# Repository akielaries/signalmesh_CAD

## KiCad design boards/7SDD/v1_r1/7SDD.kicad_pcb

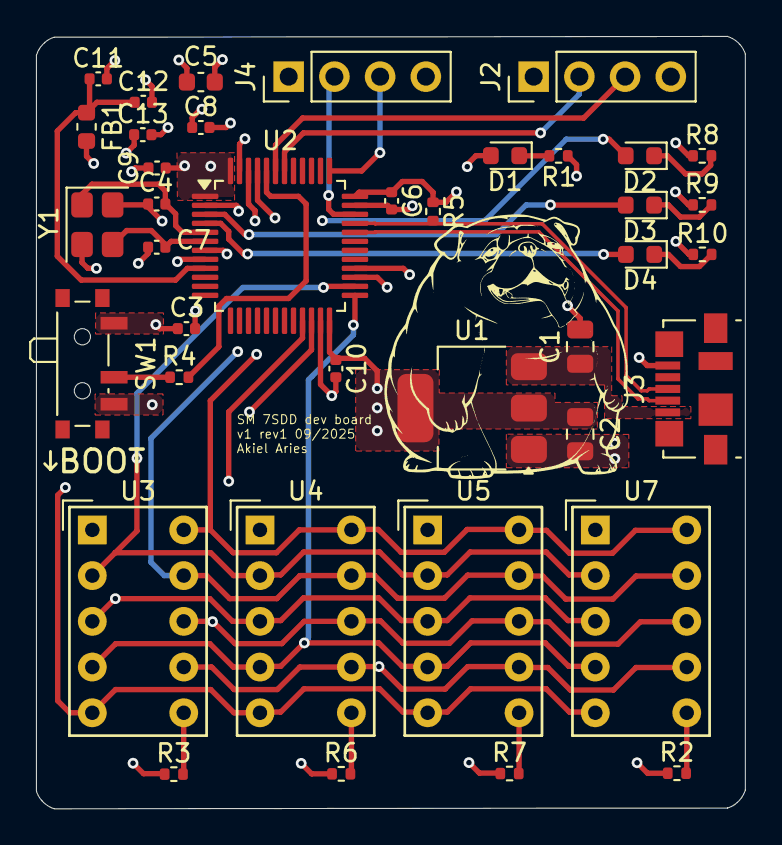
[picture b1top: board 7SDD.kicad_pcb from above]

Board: 4 copper layers, 39.4 x 42.9 mm, 39 parts (0 on the bottom side), 34 nets.

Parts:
C1, C2: 22u; C_0805_2012Metric
C3, C6, C8, C9, C10: 100n; C_0402_1005Metric
C4, C7: 10p; C_0402_1005Metric
C5: 10u; C_0603_1608Metric
C11: 10n; C_0402_1005Metric
C12, C13: 1u; C_0402_1005Metric
D1, D2: RED; LED_0603_1608Metric
D3: GREEN; LED_0603_1608Metric
D4: YEL; LED_0603_1608Metric
FB1: 120R; L_0603_1608Metric
J2: Conn_01x04_Pin; PinHeader_1x04_P2.54mm_Vertical
J3: USB_B_Micro; USB_Micro-B_Molex_47346-0001
J4: STLINK; PinHeader_1x04_P2.54mm_Vertical
R1, R8, R9, R10: 1k5; R_0402_1005Metric
R2, R3, R6, R7: 440; R_0402_1005Metric
R4: 10k; R_0402_1005Metric
R5: 1K5; R_0402_1005Metric
SW1: SW_SPDT; SW_SPDT_PCM12
U1: AMS1117-3.3; SOT-223-3_TabPin2
U2: STM32F103C8T6; LQFP-48_7x7mm_P0.5mm
U3, U4, U5, U7: HDSP-7501; HDSP-A151
Y1: 16 MHz; Crystal_SMD_3225-4Pin_3.2x2.5mm

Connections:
+3.3V: C2.1, C5.1, C6.1, C8.1, C9.1, C10.1, C13.1, D1.2 (A), FB1.2, J2.1, J4.1, R2.1, R3.1, R5.1, R6.1, R7.1, SW1.3 (C), U1.2 (VO), U2.1 (VBAT), U2.24 (VDD), U2.36 (VDD), U2.48 (VDD)
+3.3VA: C11.1, C12.1, FB1.1, U2.9 (VDDA)
/SEG_A: U2.45 (PB8), U3.10 (A), U4.10 (A), U5.10 (A), U7.10 (A)
/SEG_B: U2.46 (PB9), U3.9 (B), U4.9 (B), U5.9 (B), U7.9 (B)
/SEG_C: U2.21 (PB10), U3.8 (C), U4.8 (C), U5.8 (C), U7.8 (C)
/SEG_D: U2.22 (PB11), U3.5 (D), U4.5 (D), U5.5 (D), U7.5 (D)
/SEG_DP: U2.28 (PB15), U3.7 (DP), U4.7 (DP), U5.7 (DP), U7.7 (DP)
/SEG_E: U2.25 (PB12), U3.4 (E), U4.4 (E), U5.4 (E), U7.4 (E)
/SEG_F: U2.26 (PB13), U3.2 (F), U4.2 (F), U5.2 (F), U7.2 (F)
/SEG_G: U2.27 (PB14), U3.3 (G), U4.3 (G), U5.3 (G), U7.3 (G)
/STM32F103/BOOT0: R4.2, U2.44 (BOOT0)
/STM32F103/HSE_IN: C4.1, U2.5 (PD0), Y1.1
/STM32F103/HSE_OUT: C7.1, U2.6 (PD1), Y1.3
/STM32F103/LED1: D2.2 (A), U2.2 (PC13)
/STM32F103/LED2: D3.2 (A), U2.3 (PC14)
/STM32F103/LED3: D4.2 (A), U2.4 (PC15)
/STM32F103/NRST: C3.1, U2.7 (NRST)
/STM32F103/POWER_LED: D1.1 (K), R1.2
/STM32F103/SWCLK: J4.3, U2.37 (PA14)
/STM32F103/SWDIO: J4.2, U2.34 (PA13)
/STM32F103/SW_BOOT0: R4.1, SW1.2 (B)
/STM32F103/USART1_RX: J2.3, U2.43 (PB7)
/STM32F103/USART1_TX: J2.2, U2.42 (PB6)
/STM32F103/USB_D+: J3.3 (D+), R5.2, U2.33 (PA12)
/STM32F103/USB_D-: J3.2 (D-), U2.32 (PA11)
GND: C1.2, C2.2, C3.2, C4.2, C5.2, C6.2, C7.2, C8.2, C9.2, C10.2, C11.2, C12.2, C13.2, J2.4, J3.5 (GND), J4.4, R1.1, R8.1, R9.1, R10.1, SW1.1 (A), U1.1 (GND), U2.8 (VSSA), U2.23 (VSS), U2.35 (VSS), U2.47 (VSS), Y1.2, Y1.4
unnamed: D2.1 (K), R8.2
unnamed: D3.1 (K), R9.2
unnamed: D4.1 (K), R10.2
unnamed: R2.2, U7.6 (CA)
unnamed: R3.2, U3.6 (CA)
unnamed: R6.2, U4.6 (CA)
unnamed: R7.2, U5.6 (CA)
VBUS: C1.1, J3.1 (VBUS), U1.3 (VI)

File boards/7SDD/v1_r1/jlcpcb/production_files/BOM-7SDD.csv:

Comment,Designator,Footprint,LCSC,Quantity
100n,C3,C_0402_1005Metric,,1
1u,C12,C_0402_1005Metric,,1
1u,C13,C_0402_1005Metric,,1
RED,D2,LED_0603_1608Metric,,1
GREEN,D3,LED_0603_1608Metric,,1
1k5,R8,R_0402_1005Metric,,1
1k5,R10,R_0402_1005Metric,,1
YEL,D4,LED_0603_1608Metric,,1
1k5,R9,R_0402_1005Metric,,1
22u,C1,C_0805_2012Metric,,1
22u,C2,C_0805_2012Metric,,1
AMS1117-3.3,U1,SOT-223-3_TabPin2,,1
1k5,R1,R_0402_1005Metric,,1
10p,C7,C_0402_1005Metric,,1
10k,R4,R_0402_1005Metric,,1
100n,C9,C_0402_1005Metric,,1
16 MHz,Y1,Crystal_SMD_3225-4Pin_3.2x2.5mm,,1
10p,C4,C_0402_1005Metric,,1
120R,FB1,L_0603_1608Metric,,1
10n,C11,C_0402_1005Metric,,1
SW_SPDT,SW1,SW_SPDT_PCM12,,1
10u,C5,C_0603_1608Metric,,1
RED,D1,LED_0603_1608Metric,,1
USB_B_Micro,J3,USB_Micro-B_Molex_47346-0001,,1
100n,C8,C_0402_1005Metric,,1
HDSP-7501,U7,HDSP-A151,,1
STM32F103C8T6,U2,LQFP-48_7x7mm_P0.5mm,,1
100n,C6,C_0402_1005Metric,,1
1K5,R5,R_0402_1005Metric,,1
100n,C10,C_0402_1005Metric,,1
440,R6,R_0402_1005Metric,,1
440,R2,R_0402_1005Metric,,1
STLINK,J4,PinHeader_1x04_P2.54mm_Vertical,,1
Conn_01x04_Pin,J2,PinHeader_1x04_P2.54mm_Vertical,,1
HDSP-7501,U5,HDSP-A151,,1
HDSP-7501,U4,HDSP-A151,,1
440,R7,R_0402_1005Metric,,1
440,R3,R_0402_1005Metric,,1
HDSP-7501,U3,HDSP-A151,,1

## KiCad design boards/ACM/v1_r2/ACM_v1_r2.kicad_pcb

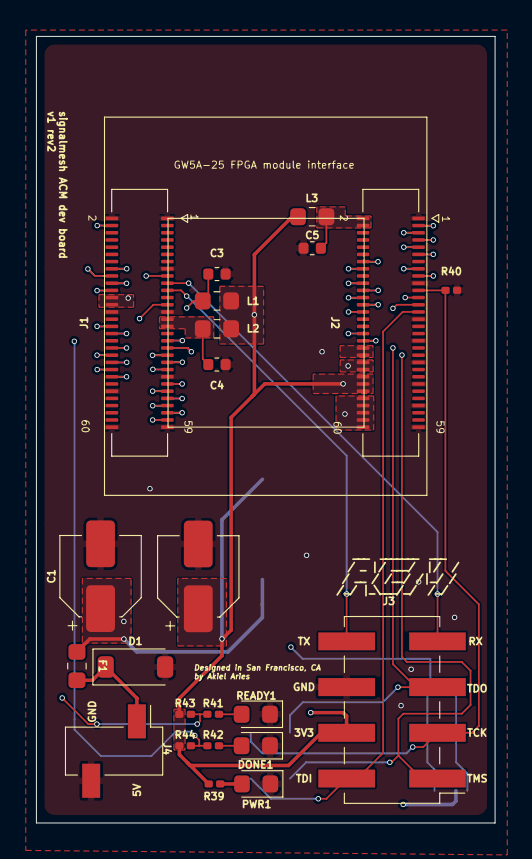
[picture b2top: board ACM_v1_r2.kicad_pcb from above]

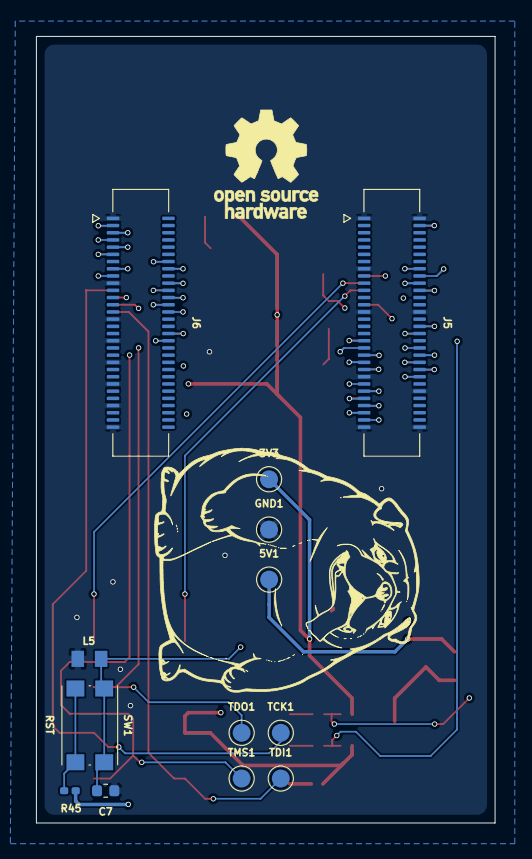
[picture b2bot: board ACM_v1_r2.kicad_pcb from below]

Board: 4 copper layers, 25.5 x 43.7 mm, 36 parts (13 on the bottom side), 66 nets.

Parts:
3V3, 5V1: TestPoint; TestPoint_Pad_D1.0mm
C1, C2: 220uF 10V; CP_Elec_4x3
C3, C4, C5, C7: 100nF; C_0402_1005Metric
D1: 20V 3A; D_SOD-123
DONE1: GREEN_LED; LED_0603_1608Metric
F1: 6V 2A; Fuse_0603_1608Metric
GND1: TestPoint; TestPoint_Pad_D1.0mm
J1, J2, J5, J6: DF40C-60DS-0.4V(51); Hirose_DF40C-60DS-0.4V_2x30_P0.4mm
J3: Conn_02x04_Odd_Even; PinHeader_2x04_P2.54mm_Vertical_SMD
J4: Conn_01x02; PinSocket_1x02_P2.54mm_Vertical_SMD_Pin1Left
L1, L2, L3: PZ1608D300-3R0TF; L_0603_1608Metric
L5: LXES15AAA1-153; INDC1005X45
PWR1: GREEN_LED; LED_0603_1608Metric
R39, R41, R42: 4.7k; R_0201_0603Metric
R40: 5.1K; R_0201_0603Metric
R43, R44: 49.9k; R_0201_0603Metric
R45: 100R; R_0201_0603Metric
READY1: GREEN_LED; LED_0603_1608Metric
SW1: RST; SW_Push_1P1T_NO_CK_KMR2
TCK1: TestPoint; TestPoint_Pad_D1.0mm
TDI1: TestPoint; TestPoint_Pad_D1.0mm
TDO1: TestPoint; TestPoint_Pad_D1.0mm
TMS1: TestPoint; TestPoint_Pad_D1.0mm

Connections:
5V_INPUT: D1.1 (K), F1.2, J4.1
+3V3: 3V3.1 (1_1), C2.1, J2.46, J2.48, J2.50, J3.4, L1.2, L2.2, L3.2, R39.2, R43.2, R44.2, R45.2
+5V: 5V1.1 (1_1), C1.1, F1.1, J2.52, J2.54, J2.56, J2.58, J2.60, J6.52, J6.54, J6.56, J6.58, J6.60
/A1_IOB24A_40P: J2.11, J6.11
/A2_JTAG_TDO: J2.25, J3.5, TDO1.1 (1_1)
/A3_JTAG_TDI: J2.27, J3.2, TDI1.1 (1_1)
/B1_JTAG_TMS: J2.23, J3.1, TMS1.1 (1_1)
/B2_IOB4A_40P: J2.3, J6.3
/B3_IOB56A_FPGA_UART_RX: J1.19, J3.7
/B10_IOL12B: J1.57, J5.57
/B11_IOL12A: J1.55, J5.55
/C1_JTAG_TCK: J2.21, J3.3, R40.1, TCK1.1 (1_1)
/C2_IOB4B_40P: J2.5, J6.5
/C3_IOB56B_FPGA_UART_TX: J1.21, J3.8
/C10_IOL5B: J1.53, J5.53
/C11_IOL5A: J1.51, J5.51
/D1_IOB14B_40P: J2.17, J6.17
/D7_DONE: J1.25, R42.2, R44.1
/D10_IOL9B: J1.49, J5.49
/D11_IOL9A: J1.47, J5.47
/E1_IOB12B_40P: J2.15, J6.15
/E8_READY: J1.17, R41.2, R43.1
/F1_IOB26B_40P: J2.9, J6.9
/F2_IOB26A_40P: J2.7, J6.7
/F5_IOT72A: J1.20, J5.20
/FMC/VCCIO0/1: J5.24, J5.26
/FMC/VCCIO2/3: J6.2, J6.4
/FMC/VCCIO6/7: J5.29, J5.31
/FMC/VDD_1V8: J6.38, J6.40
/FMC/VDD_2V5: J6.42, J6.44
/FMC/VDD_3V3: J6.46, J6.48, J6.50
/G1_IOR24B_40P: J2.20, J6.20
/G5_IOT72B: J1.22, J5.22
/G7_IOT68A: J1.16, J5.16
/G8_IOT68B: J1.18, J5.18
/G10_IOT7B: J1.43, J5.43
/G11_IOT7A: J1.41, J5.41
/H1_IOB91A_40P: J2.34, J6.34
/H2_IOB91B_40P: J2.36, J6.36
/H5_IOT61A: J1.4, J5.4
/H10_IOT3B_S2: J1.39, J5.39
/H11_IOT3A_S1: C7.2, J1.37, J5.37, L5.2, SW1.2
/J1_IOR33A_40P: J2.26, J6.26
/J2_IOR33B_40P: J2.28, J6.28
/J4_IOR22A_40P: J2.14, J6.14
/J10_IOT1B_40P: J1.35, J5.35
/K4_IOR22B_40P: J2.16, J6.16
/K6_IOT23B_USB_N: J1.32, J5.32
/K7_IOT21A_40P: J1.34, J5.34
/K10_IOT15B_40P: J1.44, J5.44
/K11_IOT11A: J1.46, J5.46
/L3_IOR31B_40P: J2.24, J6.24
/L4_IOR31A_40P: J2.22, J6.22
/L7_IOT19A_40P: J1.38, J5.38
/L8_IOT19B_40P: J1.40, J5.40
/L10_IOT15A_40P: J1.42, J5.42
/VCCIO0/1: C3.1, J1.24, J1.26, L1.1
/VCCIO2/3: C5.2, J2.2, J2.4, L3.1
/VCCIO6/7: C4.2, J1.29, J1.31, L2.1
/VDD_1V8: J2.38, J2.40
/VDD_2V5: J2.42, J2.44
GND: C1.2, C2.2, C3.2, C4.1, C5.1, C7.1, D1.2 (A), DONE1.1 (K), GND1.1 (1_1), J1.1, J1.2, J1.15, J1.27, J1.28, J1.45, J1.50, J1.59, J1.60, J2.1, J2.19, J2.29, J2.35, J2.41, J2.47, J2.53, J2.59, J3.6, J4.2, J5.1, J5.2, J5.15, J5.27, J5.28, J5.45, J5.50, J5.59, J5.60, J6.1, J6.19, J6.29, J6.35, J6.41, J6.47, J6.53, J6.59, L5.1, PWR1.1 (K), R40.2, READY1.1 (K)
unnamed: DONE1.2 (A), R42.1
unnamed: PWR1.2 (A), R39.1
unnamed: R45.1, SW1.1
unnamed: R41.1, READY1.2 (A)

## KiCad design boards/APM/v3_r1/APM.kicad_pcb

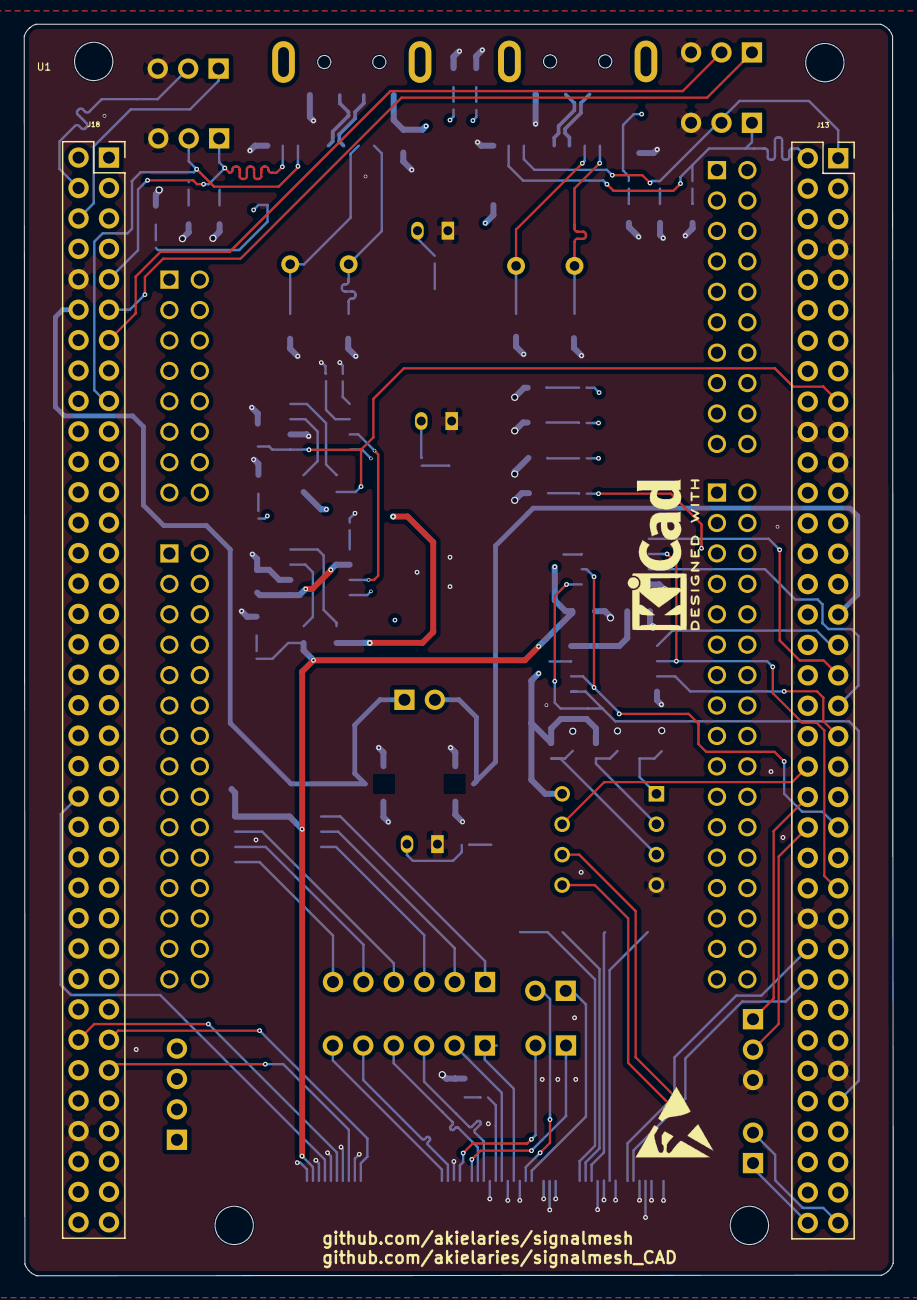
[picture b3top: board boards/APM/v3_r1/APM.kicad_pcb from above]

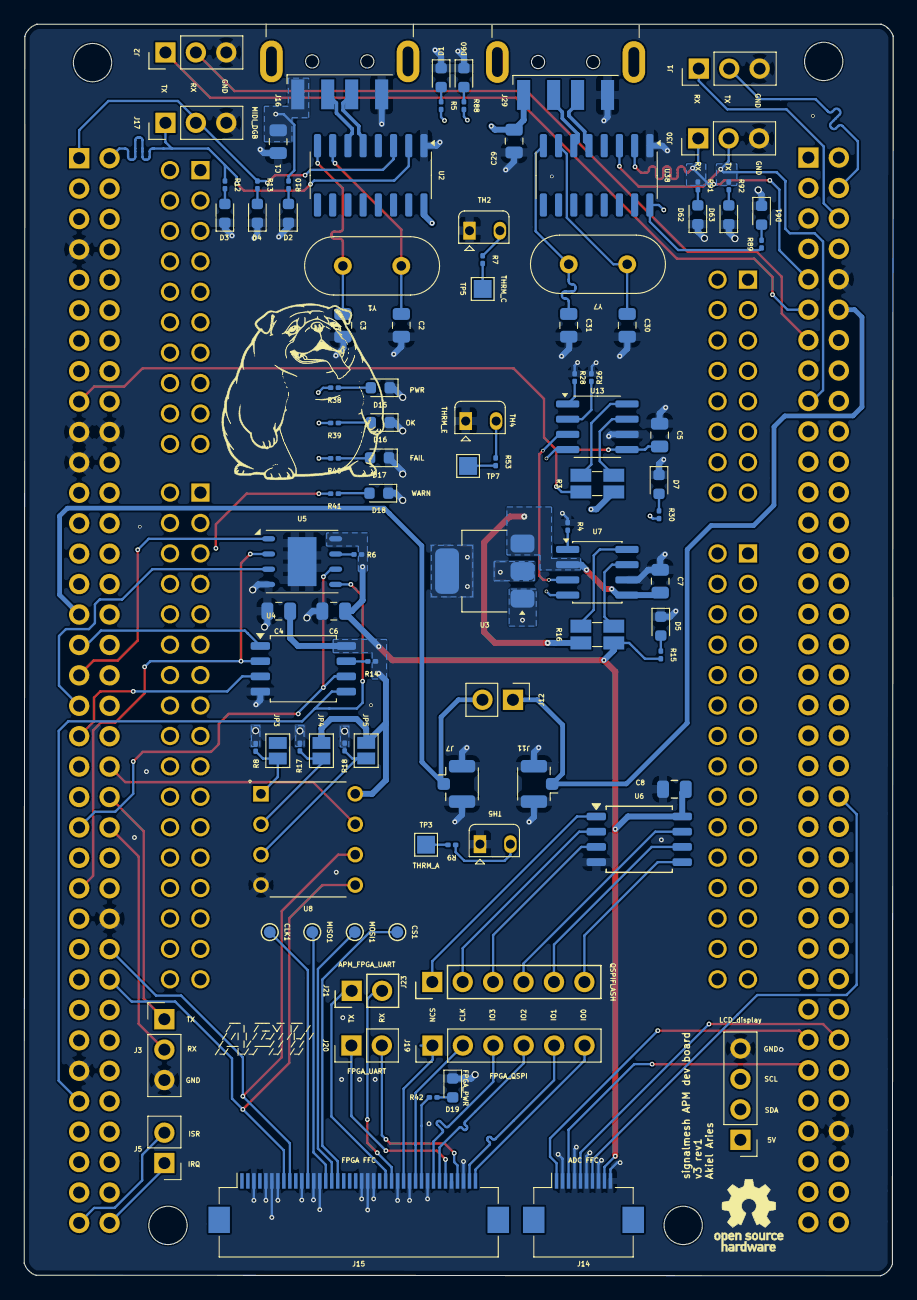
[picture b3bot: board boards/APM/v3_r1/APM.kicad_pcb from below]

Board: 4 copper layers, 72.5 x 104.5 mm, 99 parts (96 on the bottom side), 101 nets.

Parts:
C1, C2, C3, C29, C30, C31: 22pf; C_0805_2012Metric
C4, C6, C8: 100nF; C_0805_2012Metric
C5, C7: 0.1uf; C_0805_2012Metric
CLK1: TestPoint_Pad_D1.0mm
CS1: TestPoint_Pad_D1.0mm
D1, D2, D5, D7, D60, D61: LED_PWR; LED_0603_1608Metric
D3, D62: TXD; LED_0603_1608Metric
D4, D63: RXD; LED_0603_1608Metric
D15: PWR; LED_0603_1608Metric
D16: OK; LED_0603_1608Metric
D17: FAIL; LED_0603_1608Metric
D18: WARN; LED_0603_1608Metric
D19: FPGA_PWR; LED_0603_1608Metric
J1: ACM_CTRL; PinHeader_1x03_P2.54mm_Vertical
J2: CAN; PinHeader_1x03_P2.54mm_Vertical
J3: 7SDD_CTRL; PinHeader_1x03_P2.54mm_Vertical
J4: LCD_display; PinHeader_1x04_P2.54mm_Vertical
J5: INTRPT; PinHeader_1x02_P2.54mm_Vertical
J7: DAC_R_PRB; U.FL_Hirose_U.FL-R-SMT-1_Vertical
J11: DAC_L_PRB; U.FL_Hirose_U.FL-R-SMT-1_Vertical
J12: Conn_01x02; PinHeader_1x02_P2.54mm_Vertical
J13, J18: Conn_02x36_Odd_Even; PinSocket_2x36_P2.54mm_Vertical
J14: ADC FFC; Hirose_FH12-10S-0.5SH_1x10-1MP_P0.50mm_Horizontal
J15: FPGA FFC; Hirose_FH12-40S-0.5SH_1x40-1MP_P0.50mm_Horizontal
J16, J29: USB_A; USB_A_CNCTech_1001-011-01101_Horizontal
J17: MIDI_DGB; PinHeader_1x03_P2.54mm_Vertical
J19: FPGA_QSPI; PinHeader_1x06_P2.54mm_Vertical
J20: FPGA_UART; PinHeader_1x02_P2.54mm_Vertical
J21: APM_FPGA_UART; PinHeader_1x02_P2.54mm_Vertical
J23: QSPIFLASH; PinHeader_1x06_P2.54mm_Vertical
J30: UART_DEBUG; PinHeader_1x03_P2.54mm_Vertical
JP3: A0; SolderJumper-2_P1.3mm_Open_Pad1.0x1.5mm
JP4: A1; SolderJumper-2_P1.3mm_Open_Pad1.0x1.5mm
JP5: A2; SolderJumper-2_P1.3mm_Open_Pad1.0x1.5mm
MISO1: TestPoint_Pad_D1.0mm
MOSI1: TestPoint_Pad_D1.0mm
R3, R16: 0.1; R_Shunt_Ohmite_LVK12
R4, R6, R7, R8, R9, R14, R17, R18, R26, R28, R53: 10k; R_0201_0603Metric
R5, R10, R12, R13, R15, R30, R39, R40, R41, R42, R88, R91, R92: 300; R_0201_0603Metric
R38, R89: 1.2k; R_0201_0603Metric
TH2, TH4, TH5: 10k; Heraeus_TO-92-2
TP3: THRM_A; TestPoint_Pad_1.5x1.5mm
TP5: THRM_C; TestPoint_Pad_1.5x1.5mm
TP7: THRM_E; TestPoint_Pad_1.5x1.5mm
U1: NUCLEO-H753ZI; ST_Morpho_and_Zio_Connectors_144_STLink
U2, U38: CH340G; SOIC-16_3.9x9.9mm_P1.27mm
U3: LT1963AxST-3.3; SOT-223-3_TabPin2
U4, U6: W25Q128JVS; SOIC-8_5.3x5.3mm_P1.27mm
U5: MR25H40; DFN-S-8-1EP_6x5mm_P1.27mm
U7, U13: INA219AxD; SOIC-8_3.9x4.9mm_P1.27mm
U8: 24LC1025-I_P; DIP787W46P254L927H533Q8
Y1, Y7: 12MHz; Crystal_HC49-4H_Vertical

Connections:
3V3_APM: C4.1, C6.1, C8.1, J14.9, JP3.2 (B), JP4.2 (B), JP5.2 (B), R6.1, R14.1, R15.2, R16.4, U4.8 (VCC), U5.8 (VDD), U6.8 (VCC), U8.8 (VCC)
3V3_LDO: C7.2, R16.1, U3.3 (OUT), U7.2 (A0), U7.5 (VS)
5V_APM: C1.2, C29.2, J4.1, J16.1 (VBUS), J29.1 (VBUS), R3.4, R5.2, R10.2, R30.2, R38.2, R88.2, R89.2, U2.16 (VCC), U3.1 (IN), U38.16 (VCC)
5V_APM_MCU: C5.2, J13.17, R3.1, U13.5 (VS)
/7SDD_CMD_RX: J3.2, J13.46
/7SDD_CMD_TX: J3.1, J13.44
/ADC_1-2_POT_1: J14.1, J18.59
/ADC_2-2_POT_2: J14.3, J18.61
/ADC_3-5_POT_3: J14.5, J18.60
/ADC_3-6_POT_4: J14.7, J18.44
/APM_CAN_RD: J2.2, J18.13
/APM_CAN_TD: J2.1, J18.11
/APM_CMD_RX: J1.2, J18.4
/APM_CMD_TX: J1.1, J18.6
/APM_DBG_RX: J18.17, J30.2, R92.1, U38.3 (RXD)
/APM_DBG_TX: J18.9, J30.1, R91.1, U38.2 (TXD)
/APM_EEPROM_EN: J13.42, U8.7 (WP)
/APM_FPGA_UART_RX: J15.26, J21.2
/APM_FPGA_UART_TX: J15.25, J21.1
/APM_I2C1_SCL: U7.4 (SCL), U13.4 (SCL)
/APM_I2C1_SDA: U7.3 (SDA), U13.3 (SDA)
/APM_I2C2_SCL: J4.3, J13.54, J15.9, U8.6 (SCL)
/APM_I2C2_SDA: J4.2, J13.56, J15.8, U8.5 (SDA)
/APM_IRQ0: J5.1, J13.72
/APM_ISR0: J5.2, J13.71
/APM_LED_FAIL: J13.65, R41.2
/APM_LED_OK: J13.67, R39.2
/APM_LED_WARN: J13.69, R40.2
/APM_MIDI_RX: J13.1, J17.2, R13.1, U2.3 (RXD)
/APM_MIDI_TX: J13.2, J17.1, R12.1, U2.2 (TXD)
/APM_MRAM_EN: J13.37, U5.3 (~WP)
/APM_SPI1_CLK: CLK1.1 (1_1), J15.12
/APM_SPI1_CS: CS1.1 (1_1), J15.17
/APM_SPI1_MISO: J15.15, MISO1.1 (1_1)
/APM_SPI1_MOSI: J15.16, MOSI1.1 (1_1)
/APM_SPI4_MISO: J13.49, U4.2 (DO/IO_{1}), U5.2 (SO)
/APM_SPI4_MOSI: J13.63, U4.5 (DI/IO_{0}), U5.5 (SI)
/APM_SPI4_SCK: J13.45, U4.6 (CLK), U5.6 (SCK)
/APM_SPIFLASH_EN: J13.39, U4.3 (~WP/IO_{2})
/DAC_1-1_R: J7.1 (In), J12.2, J13.31
/DAC_1-2_L: J11.1 (In), J12.1, J18.12
/FPGA_UART_RX: J15.37, J20.2
/FPGA_UART_TX: J15.35, J20.1
/GCLKT_1: J15.30, J19.2
/NC: J13.25, J13.26, J13.28, J13.30, J13.70
/QSPI_IO_0: J15.40, J19.6
/QSPI_IO_1: J15.39, J19.5
/QSPI_IO_2: J15.34, J19.4
/QSPI_IO_3: J15.33, J19.3
/QSPI_NCS: J15.28, J19.1
/SPIFLASH_CS: J13.33, U4.1 (~CS)
/SPIMRAM_CS: J13.35, U5.1 (~CS)
/STORAGE_APM/QSPIFLASH_CLK: J23.5, U6.6 (CLK)
/STORAGE_APM/QSPIFLASH_CS: J23.1, U6.1 (~CS)
/STORAGE_APM/QSPIFLASH_IO0: J23.6, U6.5 (DI/IO_{0})
/STORAGE_APM/QSPIFLASH_IO1: J23.2, U6.2 (DO/IO_{1})
/STORAGE_APM/QSPIFLASH_IO2: J23.3, U6.3 (~WP/IO_{2})
/STORAGE_APM/QSPIFLASH_IO3: J23.4, U6.7 (~HOLD/~RESET/IO_{3})
/THRM_A: R9.2, TP3.1 (1_1)
/THRM_C: R7.2, TP5.1 (1_1)
/THRM_E: R53.2, TP7.1 (1_1)
/USB_MIDI_APM/D+: J16.3 (D+), U2.5 (UD+)
/USB_MIDI_APM/D-: J16.2 (D-), U2.6 (UD-)
/USB_debug_APM/D+: J29.3 (D+), U38.5 (UD+)
/USB_debug_APM/D-: J29.2 (D-), U38.6 (UD-)
FPGA_3V3_OUT1: J15.4, J15.31, R42.2
GND: C1.1, C2.2, C3.2, C4.2, C5.1, C6.2, C7.1, C8.2, C29.1, C30.2, C31.2, D1.1 (K), D2.1 (K), D3.1 (K), D4.1 (K), D5.1 (K), D7.1 (K), D15.1 (K), D16.1 (K), D17.1 (K), D18.1 (K), D19.1 (K), D60.1 (K), D61.1 (K), D62.1 (K), D63.1 (K), J1.3, J2.3, J3.3, J4.4, J7.2 (Ext), J11.2 (Ext), J13.7, J13.19, J13.20, J13.21, J13.52, J13.61, J14.2, J14.4, J14.6, J14.8, J14.10, J15.3, J15.5, J15.6, J15.7, J15.11, J15.13, J15.14, J15.21, J15.22, J15.23, J15.27, J15.29, J15.32, J15.36, J15.38, J16.4 (GND), J17.3, J18.10, J18.66, J29.4 (GND), J30.3, R4.1, R8.2, R17.2, R18.2, R26.1, R28.1, TH2.1, TH4.1, TH5.1, U2.1 (GND), U3.2 (GND), U4.4 (GND), U5.4 (VSS), U5.9 (PAD), U6.4 (GND), U7.6 (GND), U8.4 (VSS), U13.6 (GND), U38.1 (GND)
unnamed: D1.2 (A), R5.1
unnamed: D2.2 (A), R10.1
unnamed: D3.2 (A), R12.2
unnamed: D4.2 (A), R13.2
unnamed: D5.2 (A), R15.1
unnamed: D7.2 (A), R30.1
unnamed: D15.2 (A), R38.1
unnamed: D16.2 (A), R39.1
unnamed: D17.2 (A), R40.1
unnamed: D18.2 (A), R41.1
unnamed: D19.2 (A), R42.1
unnamed: D60.2 (A), R88.1
unnamed: D61.2 (A), R89.1
unnamed: D62.2 (A), R91.2
unnamed: D63.2 (A), R92.2
unnamed: JP3.1 (A), R8.1, U8.1 (A0)
unnamed: JP4.1 (A), R17.1, U8.2 (A1)
unnamed: JP5.1 (A), R18.1, U8.3 (A2)
unnamed: R7.1, TH2.2
unnamed: R9.1, TH5.2
unnamed: R53.1, TH4.2
unnamed: C2.1, U2.7 (XI), Y1.1
unnamed: C3.1, U2.8 (XO), Y1.2
unnamed: R14.2, U4.7 (~HOLD/~RESET/IO_{3})
unnamed: R6.2, U5.7 (~HOLD)
unnamed: R4.2, U7.1 (A1)
unnamed: R16.2, U7.8 (IN+)
unnamed: R16.3, U7.7 (IN-)
unnamed: R26.2, U13.2 (A0)
unnamed: R28.2, U13.1 (A1)
unnamed: R3.2, U13.8 (IN+)
unnamed: R3.3, U13.7 (IN-)
unnamed: C30.1, U38.7 (XI), Y7.1
unnamed: C31.1, U38.8 (XO), Y7.2

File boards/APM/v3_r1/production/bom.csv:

Designator,Footprint,Quantity,Value,LCSC Part #
"C1, C2, C29, C3, C30, C31",0805,6,22pf,
"C4, C6, C8",0805,3,100nF,
"C5, C7",0805,2,0.1uf,
"CLK1, CS1, MISO1, MOSI1",TestPoint_Pad_D1.0mm,4,~,
"D1, D2, D5, D60, D61, D7",0603,6,LED_PWR,
D15,0603,1,PWR,
D16,0603,1,OK,
D17,0603,1,FAIL,
D18,0603,1,WARN,
D19,0603,1,FPGA_PWR,
"D3, D62",0603,2,TXD,
"D4, D63",0603,2,RXD,
J1,PinHeader_1x03_P2.54mm_Vertical,1,ACM_CTRL,
J11,U.FL_Hirose_U.FL-R-SMT-1_Vertical,1,DAC_L_PRB,
J12,PinHeader_1x02_P2.54mm_Vertical,1,Conn_01x02,
"J13, J18",PinSocket_2x36_P2.54mm_Vertical,2,Conn_02x36_Odd_Even,
J14,Hirose_FH12-10S-0.5SH_1x10-1MP_P0.50mm_Horizontal,1,ADC FFC,
J15,Hirose_FH12-40S-0.5SH_1x40-1MP_P0.50mm_Horizontal,1,FPGA FFC,
J17,PinHeader_1x03_P2.54mm_Vertical,1,MIDI_DGB,
J19,PinHeader_1x06_P2.54mm_Vertical,1,FPGA_QSPI,
J2,PinHeader_1x03_P2.54mm_Vertical,1,CAN,
J20,PinHeader_1x02_P2.54mm_Vertical,1,FPGA_UART,
J21,PinHeader_1x02_P2.54mm_Vertical,1,APM_FPGA_UART,
J23,PinHeader_1x06_P2.54mm_Vertical,1,QSPIFLASH,
J3,PinHeader_1x03_P2.54mm_Vertical,1,7SDD_CTRL,
J30,PinHeader_1x03_P2.54mm_Vertical,1,UART_DEBUG,
J4,PinHeader_1x04_P2.54mm_Vertical,1,LCD_display,
J5,PinHeader_1x02_P2.54mm_Vertical,1,INTRPT,
J7,U.FL_Hirose_U.FL-R-SMT-1_Vertical,1,DAC_R_PRB,
"R10, R12, R13, R15, R30, R39, R40, R41, R42, R5, R88, R91, R92",0201,13,300,
"R14, R17, R18, R26, R28, R4, R53, R6, R7, R8, R9",0201,11,10k,
"R16, R3",R_Shunt_Ohmite_LVK12,2,0.1,
"R38, R89",0201,2,1.2k,
"TH2, TH4, TH5",Heraeus_TO-92-2,3,10k,
TP3,TestPoint_Pad_1.5x1.5mm,1,THRM_A,
TP5,TestPoint_Pad_1.5x1.5mm,1,THRM_C,
TP7,TestPoint_Pad_1.5x1.5mm,1,THRM_E,
U1,ST_Morpho_and_Zio_Connectors_144_STLink,1,NUCLEO-H753ZI,
"U13, U7",SOIC-8_3.9x4.9mm_P1.27mm,2,INA219AxD,
"U2, U38",SOIC-16_3.9x9.9mm_P1.27mm,2,CH340G,
U3,SOT-223-3_TabPin2,1,LT1963AxST-3.3,
"U4, U6",SOIC-8_5.3x5.3mm_P1.27mm,2,W25Q128JVS,
U5,DFN-S-8-1EP_6x5mm_P1.27mm,1,MR25H40,
U8,DIP787W46P254L927H533Q8,1,24LC1025-I_P,
"Y1, Y7",Crystal_HC49-4H_Vertical,2,12MHz,

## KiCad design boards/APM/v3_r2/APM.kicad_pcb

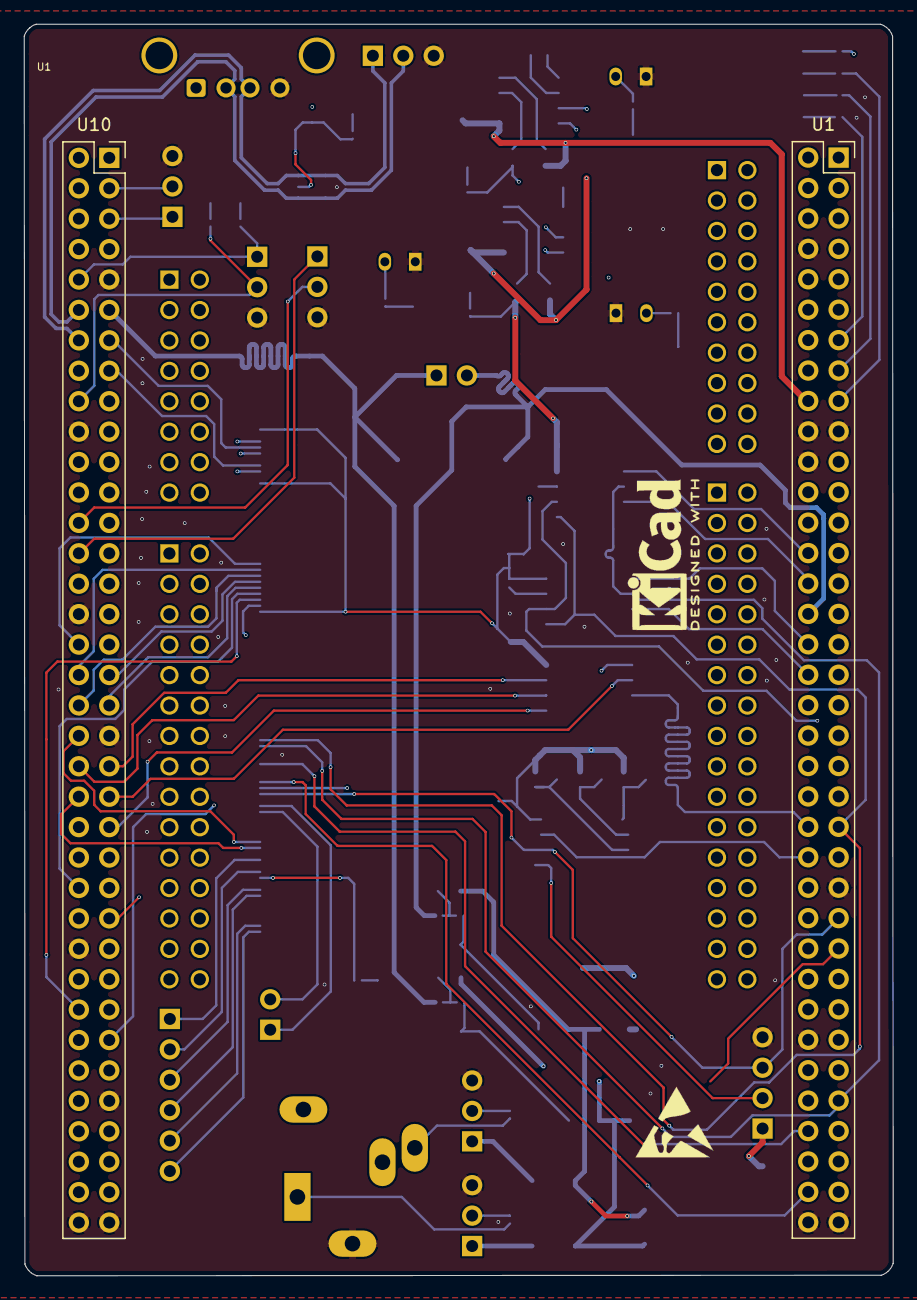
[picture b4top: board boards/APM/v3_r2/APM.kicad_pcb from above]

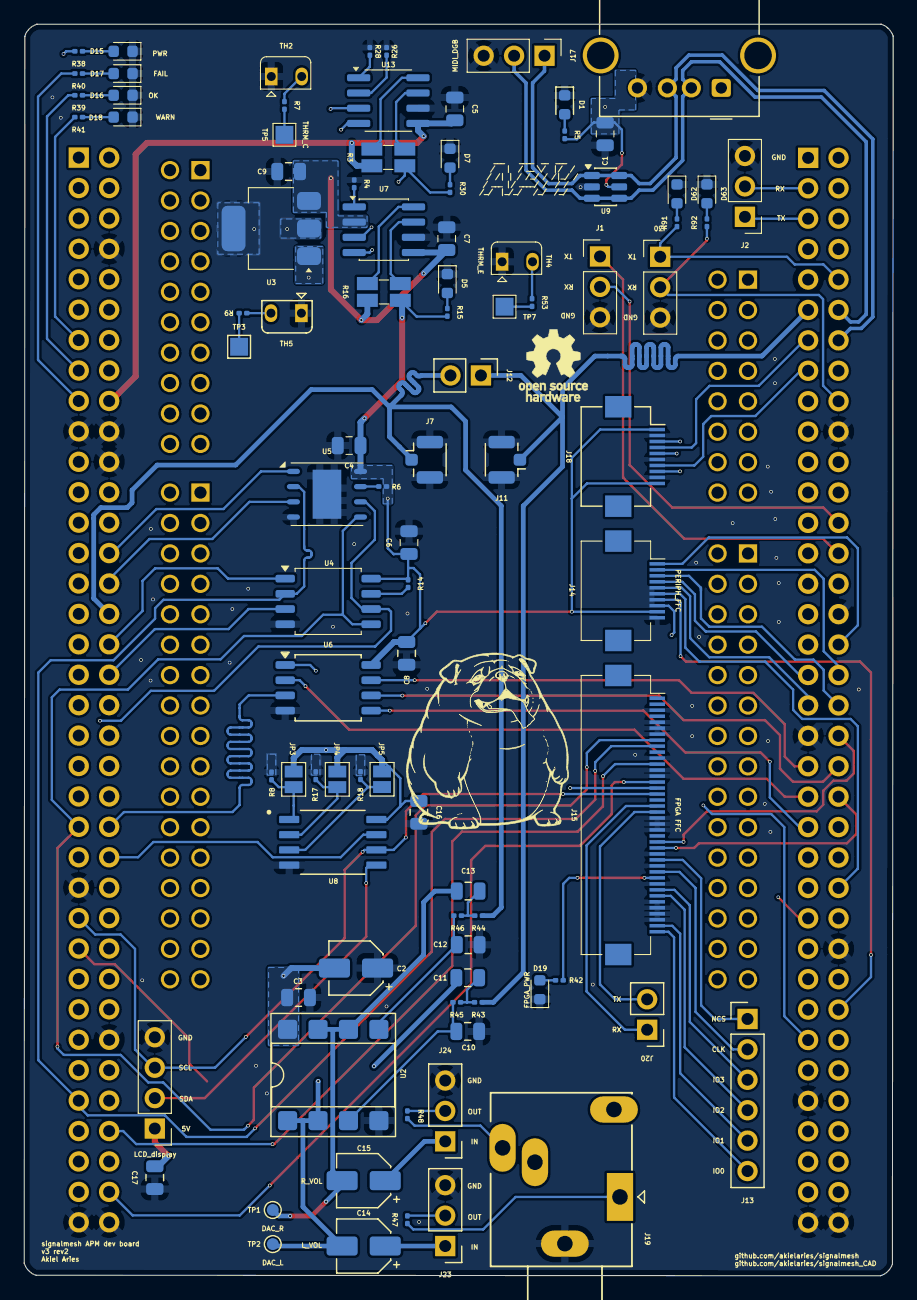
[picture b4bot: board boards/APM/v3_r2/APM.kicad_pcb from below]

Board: 4 copper layers, 72.5 x 104.5 mm, 96 parts (93 on the bottom side), 100 nets.

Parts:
C1: 22pf; C_0805_2012Metric
C2, C14, C15: 10uF; CP_Elec_4x3
C3, C4, C6, C8, C9, C16, C17: 100nF; C_0805_2012Metric
C5, C7: 0.1uf; C_0805_2012Metric
C10, C12: 2.2nF; C_0805_2012Metric
C11, C13: 4.7nF; C_0805_2012Metric
D1, D5, D7: LED_PWR; LED_0603_1608Metric
D15: PWR; LED_0603_1608Metric
D16: OK; LED_0603_1608Metric
D17: FAIL; LED_0603_1608Metric
D18: WARN; LED_0603_1608Metric
D19: FPGA_PWR; LED_0603_1608Metric
D62: TXD; LED_0603_1608Metric
D63: RXD; LED_0603_1608Metric
J1: ACM_CTRL; PinHeader_1x03_P2.54mm_Vertical
J2: CAN; PinHeader_1x03_P2.54mm_Vertical
J4: LCD_display; PinHeader_1x04_P2.54mm_Vertical
J7: DAC_R_PRB; U.FL_Hirose_U.FL-R-SMT-1_Vertical
J11: DAC_L_PRB; U.FL_Hirose_U.FL-R-SMT-1_Vertical
J12: Conn_01x02; PinHeader_1x02_P2.54mm_Vertical
J13: Conn_01x06; PinHeader_1x06_P2.54mm_Vertical
J14: POT_FFC; Hirose_FH12-10S-0.5SH_1x10-1MP_P0.50mm_Horizontal
J15: FPGA FFC; Hirose_FH12-40S-0.5SH_1x40-1MP_P0.50mm_Horizontal
J16: USB_A_FEMALE; USB_A_Molex_67643_Horizontal
J17: MIDI_DGB; PinHeader_1x03_P2.54mm_Vertical
J18: CTRL_FFC; Hirose_FH12-10S-0.5SH_1x10-1MP_P0.50mm_Horizontal
J19: AudioPlug3; Jack_3.5mm_Ledino_KB3SPRS_Horizontal
J20: FPGA_UART; PinHeader_1x02_P2.54mm_Vertical
J23: VOL_L_CTRL; PinHeader_1x03_P2.54mm_Vertical
J24: VOL_R_CTRL; PinHeader_1x03_P2.54mm_Vertical
J30: UART_DEBUG; PinHeader_1x03_P2.54mm_Vertical
JP3: A0; SolderJumper-2_P1.3mm_Open_Pad1.0x1.5mm
JP4: A1; SolderJumper-2_P1.3mm_Open_Pad1.0x1.5mm
JP5: A2; SolderJumper-2_P1.3mm_Open_Pad1.0x1.5mm
R3, R16: 0.1; R_Shunt_Ohmite_LVK12
R4, R6, R7, R8, R9, R14, R17, R18, R26, R28, R53: 10k; R_0201_0603Metric
R5, R15, R30, R39, R40, R41, R42, R91, R92: 300; R_0201_0603Metric
R38: 1.2k; R_0201_0603Metric
R43, R44, R45, R46: 2.4k; R_0201_0603Metric
R47, R48: 47; R_0201_0603Metric
TH2, TH4, TH5: 10k; Heraeus_TO-92-2
TP1: DAC_R; TestPoint_Pad_D1.0mm
TP2: DAC_L; TestPoint_Pad_D1.0mm
TP3: THRM_A; TestPoint_Pad_1.5x1.5mm
TP5: THRM_C; TestPoint_Pad_1.5x1.5mm
TP7: THRM_E; TestPoint_Pad_1.5x1.5mm
U1: NUCLEO-H753ZI; ST_Morpho_and_Zio_Connectors_144_STLink
U1#2, U10: PinSocket_2x36_P2.54mm_Vertical
U2: OPA1678; DIP-8_W7.62mm_SMDSocket_SmallPads
U3: LT1963AxST-3.3; SOT-223-3_TabPin2
U4, U6: W25Q128JVS; SOIC-8_5.3x5.3mm_P1.27mm
U5: MR25H40; DFN-S-8-1EP_6x5mm_P1.27mm
U7, U13: INA219AxD; SOIC-8_3.9x4.9mm_P1.27mm
U8: 24LC1025-I_P; SOIC127P794X202-8N
U9: USBLC6-2SC6; SOT-23-6

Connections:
3V3_APM: C4.1, C6.1, C8.1, C16.1, J14.9, J18.1, J18.10, JP3.2 (B), JP4.2 (B), JP5.2 (B), R6.1, R14.1, R15.2, R16.4, U4.8 (VCC), U5.8 (VDD), U6.8 (VCC), U8.8 (VCC)
3V3_LDO: C7.2, C9.1, R16.1, U3.3 (OUT), U7.2 (A0), U7.5 (VS)
5V_APM: C1.2, C2.2, C3.2, C17.2, J4.1, J16.1 (VBUS), R3.4, R5.2, R30.2, R38.2, U2.8 (V+), U3.1 (IN), U9.5 (VBUS)
5V_APM_MCU: C5.2, R3.1, U1#2.18 (5V), U13.5 (VS)
/ADC_POT_1: J14.1, U10.34 (PC4)
/ADC_POT_2: J14.2, U10.36 (PF5)
/ADC_POT_3: J14.3, U10.38 (PF4)
/ADC_POT_4: J14.4, U10.35 (PA2)
/ADC_POT_5: J14.5, U10.37 (PA3)
/ADC_POT_6: J14.6, U10.50 (PF14)
/ADC_POT_7: J14.7, U10.58 (PF3)
/ADC_POT_8: J14.8, U10.59 (PF12)
/APM_CAN_RD: J2.2, U10.3 (PB8)
/APM_CAN_TD: J2.1, U10.5 (PB9)
/APM_CMD_RX: J1.2, U10.26 (PB15)
/APM_CMD_TX: J1.1, U10.28 (PB14)
/APM_DBG_RX: J30.2, R92.1, U10.18 (PB11)
/APM_DBG_TX: J30.1, R91.1, U10.10 (PD8)
/APM_EEPROM_EN: U1#2.48 (PE4), U8.7 (WP)
/APM_FPGA_UART_RX: J15.25, U10.44 (PE7)
/APM_FPGA_UART_TX: J15.26, U10.40 (PE8)
/APM_I2C2_SCL: J4.3, J15.17, U1#2.51 (PF1), U7.4 (SCL), U8.6 (SCL), U13.4 (SCL)
/APM_I2C2_SDA: J4.2, J15.16, U1#2.53 (PF0), U7.3 (SDA), U8.5 (SDA), U13.3 (SDA)
/APM_LED_FAIL: R41.2, U1#2.13 (PA13)
/APM_LED_OK: R39.2, U1#2.15 (PA14)
/APM_LED_WARN: R40.2, U1#2.17 (PA15)
/APM_MRAM_EN: U1#2.30 (PA1), U5.3 (~WP)
/APM_SPI1_CS: J15.12, U1#2.66 (PG10)
/APM_SPI1_MISO: J15.9, U1#2.63 (PG9), U4.2 (DO/IO_{1}), U5.2 (SO)
/APM_SPI1_MOSI: J15.8, U1#2.45 (PD7), U4.5 (DI/IO_{0}), U5.5 (SI)
/APM_SPI1_SCK: J15.15, U1#2.70 (PG11), U4.6 (CLK), U5.6 (SCK)
/APM_SPI4_MISO: J18.5, U10.55 (PE13)
/APM_SPI4_MOSI: J18.8, U10.51 (PE14)
/APM_SPI4_SCK: J18.3, U10.49 (PE12)
/APM_SPIFLASH_EN: U1#2.36 (PC1), U4.3 (~WP/IO_{2})
/AUDIO_APM/OUT_L: J23.2, R47.2
/AUDIO_APM/OUT_R: J24.2, R48.2
/AUDIO_APM/VOL_L_IN: C14.1, J23.1
/AUDIO_APM/VOL_R_IN: C15.1, J24.1
/DAC_1-1_R: J7.1 (In), J12.2, R44.1, U1#2.32 (PA4)
/DAC_1-2_L: J11.1 (In), J12.1, R43.1, U10.11 (PA5)
/FPGA_UART_RX: J15.20, J20.2
/FPGA_UART_TX: J15.19, J20.1
/GCLKT_1: J13.2, J15.30
/MIDI_FS_D+: J16.3 (D+), J17.1, U9.1 (I/O1), U9.6 (I/O1), U10.14 (PA11)
/MIDI_FS_D-: J16.2 (D-), J17.2, U9.3 (I/O2), U9.4 (I/O2), U10.12 (PA12)
/NC: U1#2.25 (PC14), U1#2.27 (PC15), U1#2.29 (PH0)
/QSPI1_D0: U6.5 (DI/IO_{0}), U10.45 (PD11)
/QSPI1_D1: U6.2 (DO/IO_{1}), U10.43 (PD12)
/QSPI1_D2: U1#2.46 (PE2), U6.3 (~WP/IO_{2})
/QSPI1_D3: U6.7 (~HOLD/~RESET/IO_{3}), U10.41 (PD13)
/QSPI1_NCS: U6.1 (~CS), U10.70 (PG6)
/QSPI_IO_0: J13.6, J15.40
/QSPI_IO_1: J13.5, J15.39
/QSPI_IO_2: J13.4, J15.34
/QSPI_IO_3: J13.3, J15.33
/QSPI_NCS: J13.1, J15.28
/QSPI_SCK2: U6.6 (CLK), U10.42 (PF10)
/SPIFLASH_CS: U1#2.34 (PB0), U4.1 (~CS)
/SPIMRAM_CS: U1#2.28 (PA0), U5.1 (~CS)
/SR_GPIO1: J18.4, U10.13 (PA6)
/SR_GPIO2: J18.7, U10.15 (PA7)
/THRM_A: R9.2, TP3.1 (1_1)
/THRM_C: R7.2, TP5.1 (1_1)
/THRM_E: R53.2, TP7.1 (1_1)
DAC_L_OUT: C11.1, C14.2, TP2.1 (1_1), U2.1, U2.2 (-)
DAC_R_OUT: C13.1, C15.2, TP1.1 (1_1), U2.6 (-), U2.7
FPGA_3V3_OUT1: J15.4, J15.31, R42.2
GND: C1.1, C2.1, C3.1, C4.2, C5.1, C6.2, C7.1, C8.2, C9.2, C10.1, C12.1, C16.2, C17.1, D1.1 (K), D5.1 (K), D7.1 (K), D15.1 (K), D16.1 (K), D17.1 (K), D18.1 (K), D19.1 (K), D62.1 (K), D63.1 (K), J1.3, J2.3, J4.4, J7.2 (Ext), J11.2 (Ext), J14.10, J15.3, J15.5, J15.6, J15.7, J15.11, J15.13, J15.14, J15.21, J15.22, J15.23, J15.27, J15.29, J15.32, J15.35, J15.36, J15.37, J15.38, J16.4 (GND), J17.3, J18.2, J18.6, J18.9, J19.S, J23.3, J24.3, J30.3, R4.1, R8.2, R17.2, R18.2, R26.1, R28.1, TH2.1, TH4.1, TH5.1, U1#2.8 (GND_CN11), U1#2.19 (GND_CN11), U1#2.20 (GND_CN11), U1#2.22 (GND_CN11), U1#2.49 (GND_CN11), U1#2.60 (GND_CN11), U1#2.71 (GND_CN11), U1#2.72 (GND_CN11), U2.4 (V-), U3.2 (GND), U4.4 (GND), U5.4 (VSS), U5.9 (PAD), U6.4 (GND), U7.6 (GND), U8.4 (VSS), U9.2 (GND), U10.9 (GND_CN12), U10.20 (GND_CN12), U10.32 (AGND_CN12), U10.39 (GND_CN12), U10.54 (GND_CN12), U10.63 (GND_CN12), U10.71 (GND_CN12), U10.72 (GND_CN12), U13.6 (GND)
unnamed: C11.2, R43.2, R45.1
unnamed: C13.2, R44.2, R46.1
unnamed: D1.2 (A), R5.1
unnamed: D5.2 (A), R15.1
unnamed: D7.2 (A), R30.1
unnamed: D15.2 (A), R38.1
unnamed: D16.2 (A), R39.1
unnamed: D17.2 (A), R40.1
unnamed: D18.2 (A), R41.1
unnamed: D19.2 (A), R42.1
unnamed: D62.2 (A), R91.2
unnamed: D63.2 (A), R92.2
unnamed: J19.R, R48.1
unnamed: J19.T, R47.1
unnamed: JP3.1 (A), R8.1, U8.1 (A0)
unnamed: JP4.1 (A), R17.1, U8.2 (A1)
unnamed: JP5.1 (A), R18.1, U8.3 (A2)
unnamed: R7.1, TH2.2
unnamed: R9.1, TH5.2
unnamed: R53.1, TH4.2
unnamed: C10.2, R45.2, U2.3 (+)
unnamed: C12.2, R46.2, U2.5 (+)
unnamed: R14.2, U4.7 (~HOLD/~RESET/IO_{3})
unnamed: R6.2, U5.7 (~HOLD)
unnamed: R4.2, U7.1 (A1)
unnamed: R16.2, U7.8 (IN+)
unnamed: R16.3, U7.7 (IN-)
unnamed: R26.2, U13.2 (A0)
unnamed: R28.2, U13.1 (A1)
unnamed: R3.2, U13.8 (IN+)
unnamed: R3.3, U13.7 (IN-)

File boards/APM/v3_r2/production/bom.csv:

Designator,Footprint,Quantity,Value,LCSC Part #
C1,0805,1,22pf,
"C10, C12",0805,2,2.2nF,
"C11, C13",0805,2,4.7nF,
"C14, C15, C2",CP_Elec_4x3,3,10uF,
"C16, C17, C3, C4, C6, C8, C9",0805,7,100nF,
"C5, C7",0805,2,0.1uf,
"D1, D5, D7",0603,3,LED_PWR,
D15,0603,1,PWR,
D16,0603,1,OK,
D17,0603,1,FAIL,
D18,0603,1,WARN,
D19,0603,1,FPGA_PWR,
D62,0603,1,TXD,
D63,0603,1,RXD,
J1,PinHeader_1x03_P2.54mm_Vertical,1,ACM_CTRL,
J11,U.FL_Hirose_U.FL-R-SMT-1_Vertical,1,DAC_L_PRB,
J12,PinHeader_1x02_P2.54mm_Vertical,1,Conn_01x02,
J13,PinHeader_1x06_P2.54mm_Vertical,1,Conn_01x06,
J14,Hirose_FH12-10S-0.5SH_1x10-1MP_P0.50mm_Horizontal,1,POT_FFC,
J15,Hirose_FH12-40S-0.5SH_1x40-1MP_P0.50mm_Horizontal,1,FPGA FFC,
J16,USB_A_Molex_67643_Horizontal,1,USB_A_FEMALE,
J17,PinHeader_1x03_P2.54mm_Vertical,1,MIDI_DGB,
J18,Hirose_FH12-10S-0.5SH_1x10-1MP_P0.50mm_Horizontal,1,CTRL_FFC,
J19,Jack_3.5mm_Ledino_KB3SPRS_Horizontal,1,AudioPlug3,
J2,PinHeader_1x03_P2.54mm_Vertical,1,CAN,
J20,PinHeader_1x02_P2.54mm_Vertical,1,FPGA_UART,
J23,PinHeader_1x03_P2.54mm_Vertical,1,VOL_L_CTRL,
J24,PinHeader_1x03_P2.54mm_Vertical,1,VOL_R_CTRL,
J30,PinHeader_1x03_P2.54mm_Vertical,1,UART_DEBUG,
J4,PinHeader_1x04_P2.54mm_Vertical,1,LCD_display,
J7,U.FL_Hirose_U.FL-R-SMT-1_Vertical,1,DAC_R_PRB,
"R14, R17, R18, R26, R28, R4, R53, R6, R7, R8, R9",0201,11,10k,
"R15, R30, R39, R40, R41, R42, R5, R91, R92",0201,9,300,
"R16, R3",R_Shunt_Ohmite_LVK12,2,0.1,
R38,0201,1,1.2k,
"R43, R44, R45, R46",0201,4,2.4k,
"R47, R48",0201,2,47,
"TH2, TH4, TH5",Heraeus_TO-92-2,3,10k,
TP1,TestPoint_Pad_D1.0mm,1,DAC_R,
TP2,TestPoint_Pad_D1.0mm,1,DAC_L,
TP3,TestPoint_Pad_1.5x1.5mm,1,THRM_A,
TP5,TestPoint_Pad_1.5x1.5mm,1,THRM_C,
TP7,TestPoint_Pad_1.5x1.5mm,1,THRM_E,
U1_2,ST_Morpho_and_Zio_Connectors_144_STLink,1,NUCLEO-H753ZI,
"U1, U10",PinSocket_2x36_P2.54mm_Vertical,2,~,
"U13, U7",SOIC-8_3.9x4.9mm_P1.27mm,2,INA219AxD,
U2,DIP-8_W7.62mm_SMDSocket_SmallPads,1,OPA1678,
U3,SOT-223-3_TabPin2,1,LT1963AxST-3.3,
"U4, U6",SOIC-8_5.3x5.3mm_P1.27mm,2,W25Q128JVS,
U5,DFN-S-8-1EP_6x5mm_P1.27mm,1,MR25H40,
U8,SOIC127P794X202-8N,1,24LC1025-I_P,
U9,SOT-23-6,1,USBLC6-2SC6,
